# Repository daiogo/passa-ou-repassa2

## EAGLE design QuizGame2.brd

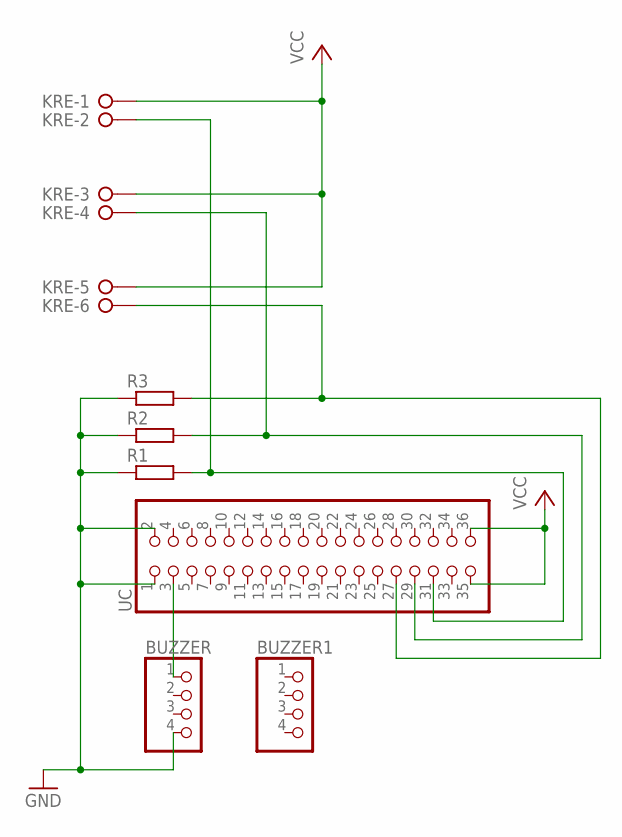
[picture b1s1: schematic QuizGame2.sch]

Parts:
BUZZER, BUZZER1: PINHD-1X4; 1X04
KRE: W237-06P; W237-6P
R1, R2, R3: R-EU_0207/12; 0207/12
UC: PINHD-2X18; 2X18

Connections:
GND: BUZZER.4, R1.1, R2.1, R3.1, UC.1, UC.2
unnamed: KRE.2, R1.2, UC.31
unnamed: KRE.4, R2.2, UC.29
unnamed: KRE.6, R3.2, UC.27
unnamed: BUZZER.1, UC.3
VCC: KRE.1, KRE.3, KRE.5, UC.35, UC.36

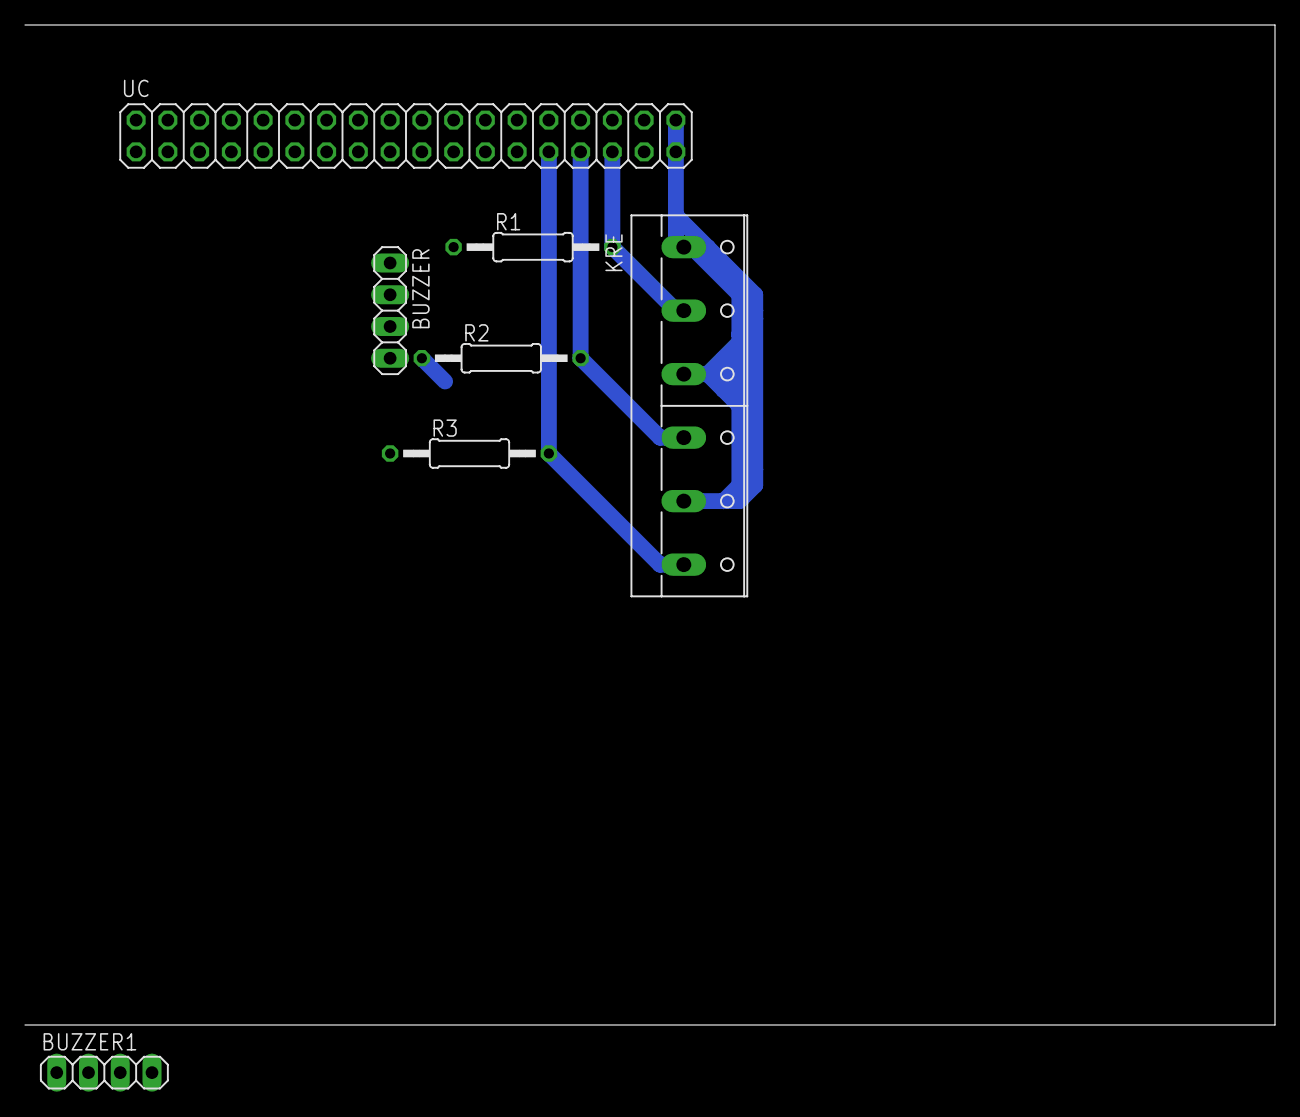
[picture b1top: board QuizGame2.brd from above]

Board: 2 copper layers, 100.0 x 80.0 mm, 7 parts (0 on the bottom side), 6 nets.

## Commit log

2023-01-14 Added board schematics
